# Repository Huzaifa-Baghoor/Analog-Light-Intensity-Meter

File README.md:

# Analog Light Intensity Meter

I wanted to make some projects without microcontroller so I made this **light intensity meter** which indicates light in 10 distinct levels.

## Working

The **LM324N IC** contains 4 OpAmps which are being used as Comparaters. They compare two voltages i.e. **reference voltage** and **signal voltage** and  if signal voltage is higher than reference voltage the output is on and all the LEDs till that level turn on.

## PCB and Connections

The Project is powered by a 9V source the thee +9V goes to the VCC of op Amps and top of the voltage divider bridge and top of the sensitivity control area the Gnd goes to the GND of op Amps and bottom of the voltage divider bridge and bottom of the sensitivity control area . The signal from the senstivity control area goes to the +ve of op amps and the 10 voltage levels are connected to -ve of 10 individual op Amps.

**The PCB isn't working but if you try to make it on breadboard using the same schematics then it works fine.**

|Schematics|Tracks|
| :---: | :---: |
|  |  |

## Bill of Materials (BOM)

| Name | Purpose | Quantity | Total Cost (USD) | Link | Distributor |
| :---: | :---: | :---: | :---: | :---: | :---: | 
| LEDs | Indicator | 10 | 7 | [LED](https://www.aliexpress.com/item/1005003337390606.html?spm=a2g0o.cart.0.0.12d438daRTPLv9&mp=1&pdp_npi=6%40dis%21USD%21USD%206.68%21USD%206.68%21%21USD%206.68%21%21%21%402141131717759137152123058eb796%2112000025287186811%21ct%21PK%212961473668%21%211%210%21) | AliExpress |
| PCB | to assemble the project | 1 | 35 | [PCB](https://cart.jlcpcb.com/quote/gerberviewThree/?qs=edae4f3f128a488bbbc25f9c6c296d6c_1_0_1_0_0.html) | AliExpress
| IC Base | to solder ICs on PCB or Veroboard |  | 2 | [IC Base](https://www.aliexpress.com/item/32866483409.html?spm=a2g0o.cart.0.0.12d438daRTPLv9&mp=1&pdp_npi=6%40dis%21USD%21USD%202.53%21USD%202.53%21%21USD%202.50%21%21%21%402141131717759137152123058eb796%2165442005257%21ct%21PK%212961473668%21%211%210%21) | AliExpress |
| Potentiometer | Control Senstivity | 1 | 3 | [Potentiometer](https://www.aliexpress.com/item/1005007730415902.html?spm=a2g0o.cart.0.0.12d438daRTPLv9&mp=1&pdp_npi=6%40dis%21USD%21USD%205.09%21USD%203.91%21%21USD%203.87%21%21%21%402141131717759137152123058eb796%2112000042014621765%21ct%21PK%212961473668%21%211%210%21) | AliExpress |
| LDR | Detecting Light level | 1 | 3 | [LDR](https://www.aliexpress.com/item/1005010362917938.html?spm=a2g0o.cart.0.0.12d438daRTPLv9&mp=1&pdp_npi=6%40dis%21USD%21USD%206.96%21USD%203.34%21%21USD%203.31%21%21%21%402141131717759137152123058eb796%2112000052228563358%21ct%21PK%212961473668%21%211%210%21) | AliExpress |
| 1kΩ Resistor | For Voltage Divider Bridge | 11 | 2 | [1K Resistor](https://www.aliexpress.com/item/1005009177180559.html?spm=a2g0o.cart.0.0.12d438daRTPLv9&mp=1&pdp_npi=6%40dis%21USD%21USD%202.16%21USD%202.16%21%21USD%202.09%21%21%21%402141131717759137152123058eb796%2112000048205104387%21ct%21PK%212961473668%21%211%210%21) | AliExpress |
| 470Ω Resistor | for LEDs | 10 | 2 | [470R Resistor](https://www.aliexpress.com/item/1005009177180559.html?spm=a2g0o.cart.0.0.12d438daRTPLv9&mp=1&pdp_npi=6%40dis%21USD%21USD%202.16%21USD%202.16%21%21USD%202.10%21%21%21%402141131717759137152123058eb796%2112000048205104379%21ct%21PK%212961473668%21%211%210%21) | AliExpress |
| LM324N | Quad OpAmp ICs | 6 | 7 | [LM324N IC](https://www.aliexpress.com/item/1005008583669771.html?spm=a2g0o.cart.0.0.12d438daRTPLv9&mp=1&pdp_npi=6%40dis%21USD%21USD%202.28%21USD%202.28%21%21USD%202.17%21%21%21%402141131717759137152123058eb796%2112000045869429620%21ct%21PK%212961473668%21%211%210%21&pdp_ext_f=%7B%22cart2PdpParams%22%3A%7B%22pdpBusinessMode%22%3A%22retail%22%7D%7D) | AliExpress |

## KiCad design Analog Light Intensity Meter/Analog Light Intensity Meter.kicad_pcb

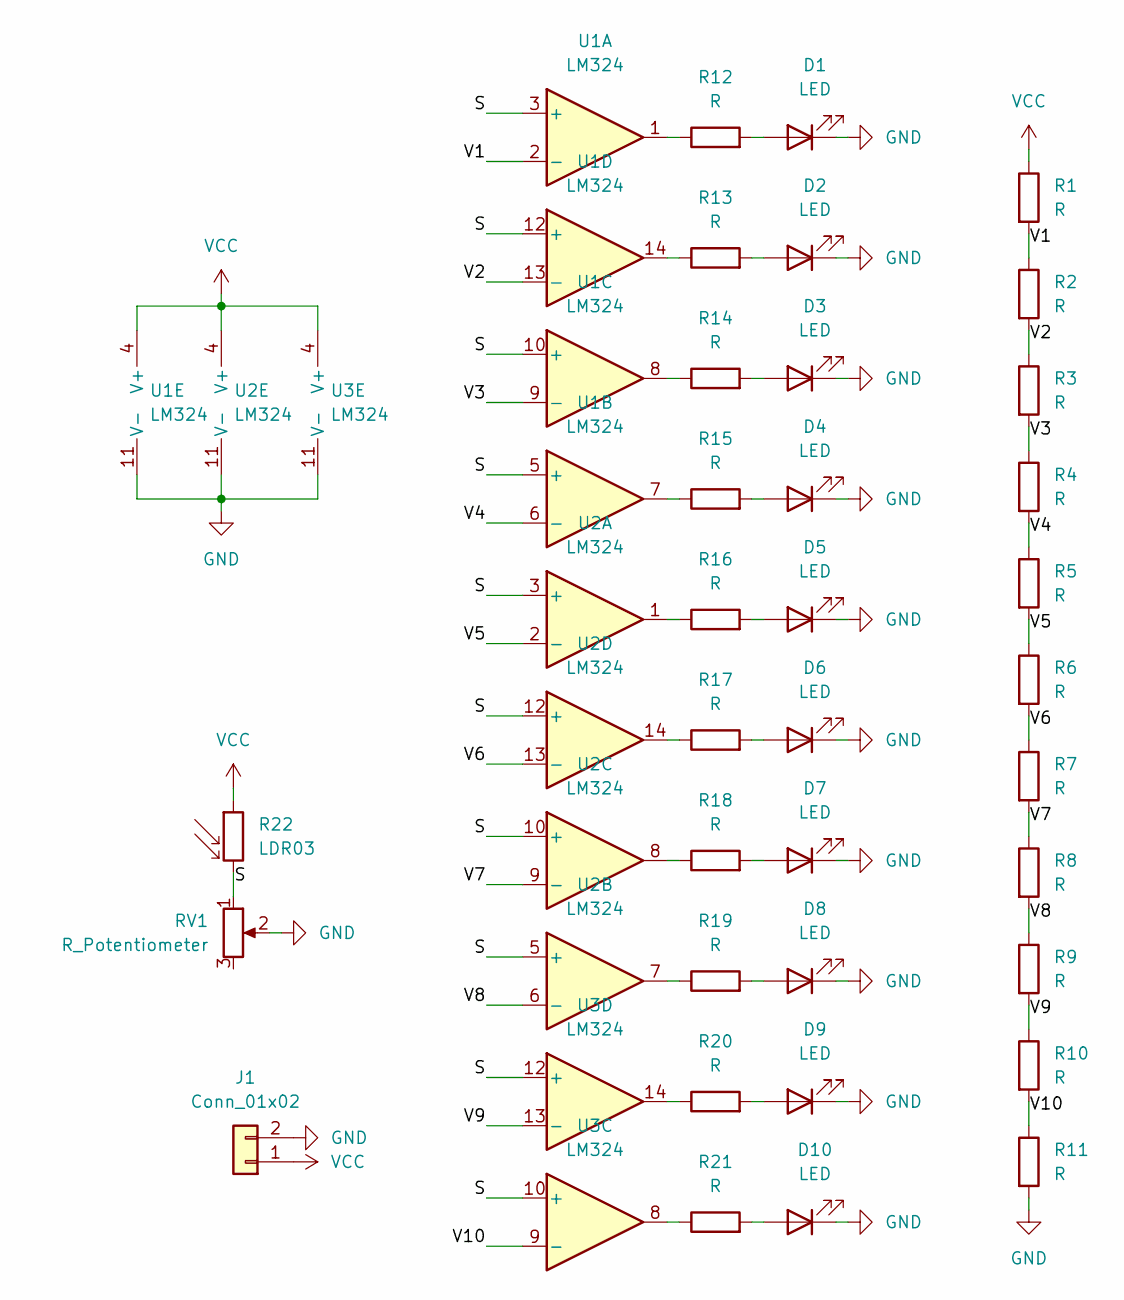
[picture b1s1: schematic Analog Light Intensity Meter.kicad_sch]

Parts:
D1, D2, D3, D4, D5, D6, D7, D8, D9, D10: LED; LED_D5.0mm
J1: Conn_01x02; TerminalBlock_Phoenix_MKDS-1,5-2-5.08_1x02_P5.08mm_Horizont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
R1, R2, R3, R4, R5, R6, R7, R8, R9, R10, R11, R12, R13, R14, R15, R16, R17, R18, R19, R20, R21: R; R_Axial_DIN0207_L6.3mm_D2.5mm_P7.62mm_Horizontal
R22: LDR03; R_LDR_10x8.5mm_P7.6mm_Vertical
RV1: R_Potentiometer; Potentiometer_Alps_RK163_Single_Horizontal
U1, U2: LM324; DIP-14_W7.62mm_LongPads
U3: LM324

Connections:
/S: R22.2, RV1.1, U1.3 (+), U1.5 (+), U1.10 (+), U1.12 (+), U2.3 (+), U2.5 (+), U2.10 (+), U2.12 (+), U3.10 (+), U3.12 (+)
/V1: R1.2, R2.1, U1.2 (-)
/V2: R2.2, R3.1, U1.13 (-)
/V3: R3.2, R4.1, U1.9 (-)
/V4: R4.2, R5.1, U1.6 (-)
/V5: R5.2, R6.1, U2.2 (-)
/V6: R6.2, R7.1, U2.13 (-)
/V7: R7.2, R8.1, U2.9 (-)
/V8: R8.2, R9.1, U2.6 (-)
/V9: R9.2, R10.1, U3.13 (-)
/V10: R10.2, R11.1, U3.9 (-)
GND: D1.1 (K), D2.1 (K), D3.1 (K), D4.1 (K), D5.1 (K), D6.1 (K), D7.1 (K), D8.1 (K), D9.1 (K), D10.1 (K), J1.2, R11.2, RV1.2, U1.11 (V-), U2.11 (V-), U3.11 (V-)
unnamed: D1.2 (A), R12.2
unnamed: D2.2 (A), R13.2
unnamed: D3.2 (A), R14.2
unnamed: D4.2 (A), R15.2
unnamed: D5.2 (A), R16.2
unnamed: D6.2 (A), R17.2
unnamed: D7.2 (A), R18.2
unnamed: D8.2 (A), R19.2
unnamed: D9.2 (A), R20.2
unnamed: D10.2 (A), R21.2
unnamed: R12.1, U1.1
unnamed: R13.1, U1.14
unnamed: R14.1, U1.8
unnamed: R15.1, U1.7
unnamed: R16.1, U2.1
unnamed: R17.1, U2.14
unnamed: R18.1, U2.8
unnamed: R19.1, U2.7
unnamed: R20.1, U3.14
unnamed: R21.1, U3.8
VCC: J1.1, R1.1, R22.1, U1.4 (V+), U2.4 (V+), U3.4 (V+)

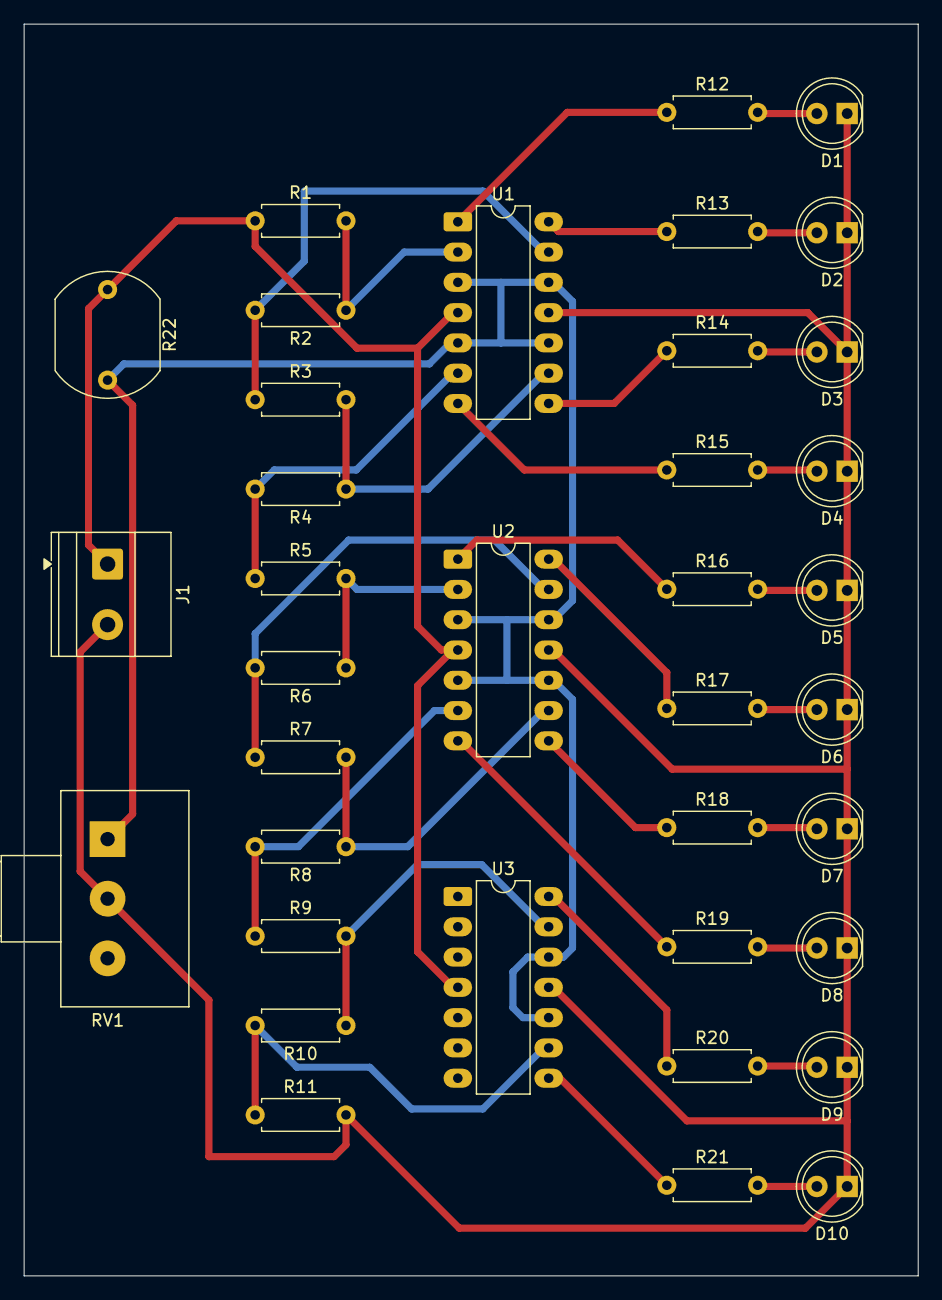
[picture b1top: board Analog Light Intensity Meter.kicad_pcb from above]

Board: 2 copper layers, 75.0 x 105.0 mm, 37 parts (0 on the bottom side), 33 nets.

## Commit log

2026-04-11 Updated Readme and BOM.csv added
